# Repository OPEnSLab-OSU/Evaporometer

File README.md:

# OPEnS Lab Evaporometer

Here are documented all of the files and links regarding the evapor0meter. This includes all of code and CAD files to create and program the entire system. It also includes a link to the lastest data collected in the field. 

For an overview of the project view the [Evaporometer Wiki](https://github.com/OPEnSLab-OSU/OPEnS-Lab-Home/wiki/Evaporometer)

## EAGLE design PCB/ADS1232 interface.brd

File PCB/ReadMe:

Place to store archived EagleCAD PCB projects. Files shoudl have last data modified and version number in the name.

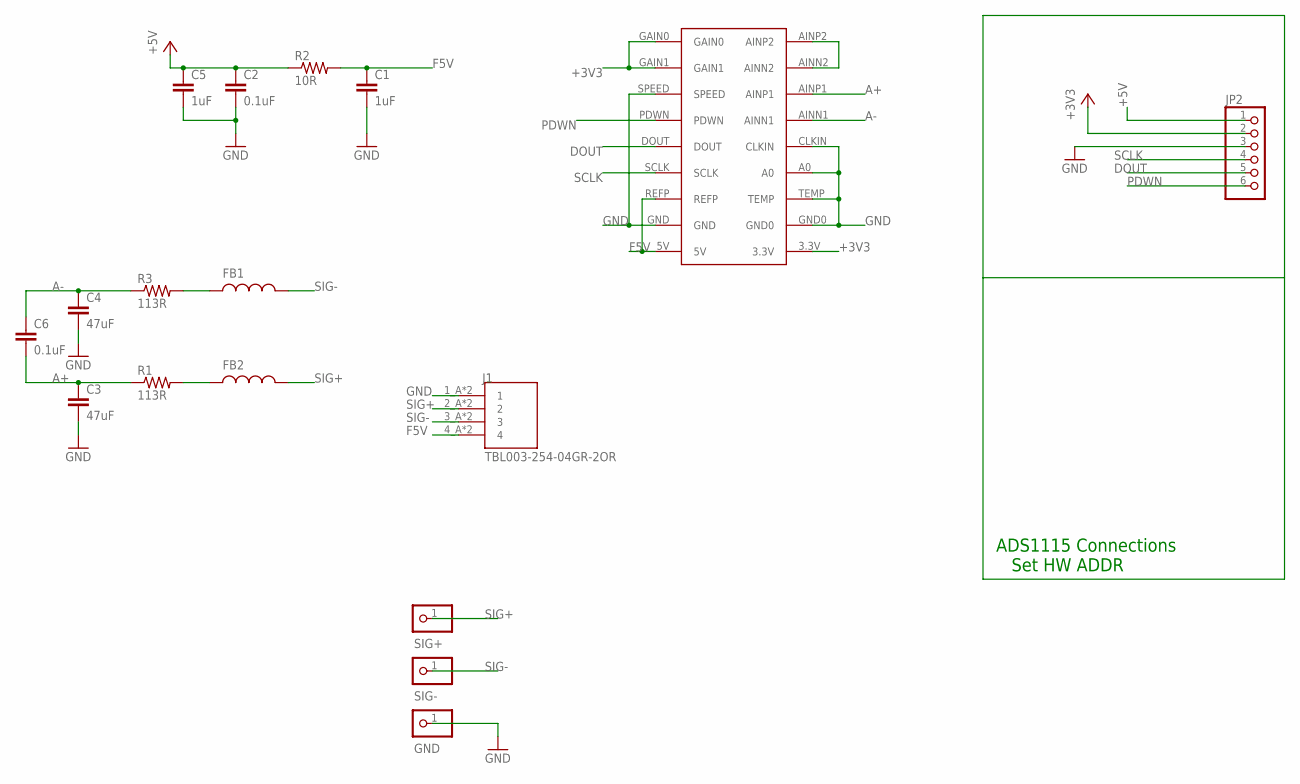
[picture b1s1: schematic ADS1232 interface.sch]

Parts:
ADS1232: ADS1232
C1, C5: 1uF; C0805
C2, C6: 0.1uF; C0805
C3, C4: 47uF; C0805
FB1, FB2: WE-RFI_0805A_744760282A; WE-RFI_0805A
GND: PINHD-1X1; 1X01
J1: TBL003-254-04GR-2OR; CUI_TBL003-254-04GR-2OR
JP2: PINHD-1X6; 1X06
R1, R3: 113R; R0805
R2: 10R; R0805
SIG+: PINHD-1X1; 1X01
SIG-: PINHD-1X1; 1X01

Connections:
+3V3: ADS1232.3.3V, ADS1232.GAIN0, ADS1232.GAIN1, JP2.2
+5V: C2.1, C5.1, JP2.1, R2.1
A+: ADS1232.AINP1, C3.1, C6.2, R1.1
A-: ADS1232.AINN1, C4.1, C6.1, R3.1
DOUT: ADS1232.DOUT, JP2.5
F5V: ADS1232.5V, ADS1232.REFP, C1.1, J1.4_A (4), J1.4_B (4), R2.2
GND: ADS1232.A0, ADS1232.AINN2, ADS1232.AINP2, ADS1232.CLKIN, ADS1232.GND, ADS1232.GND0, ADS1232.SPEED, ADS1232.TEMP, C1.2, C2.2, C3.2, C4.2, C5.2, GND.1, J1.1_A (1), J1.1_B (1), JP2.3
unnamed: FB1.1, R3.2
unnamed: FB2.1, R1.2
PDWN: ADS1232.PDWN, JP2.6
SCLK: ADS1232.SCLK, JP2.4
SIG+: FB2.2, J1.2_A (2), J1.2_B (2), SIG+.1
SIG-: FB1.2, J1.3_A (3), J1.3_B (3), SIG-.1

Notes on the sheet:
ADS1115 Connections Set HW ADDR

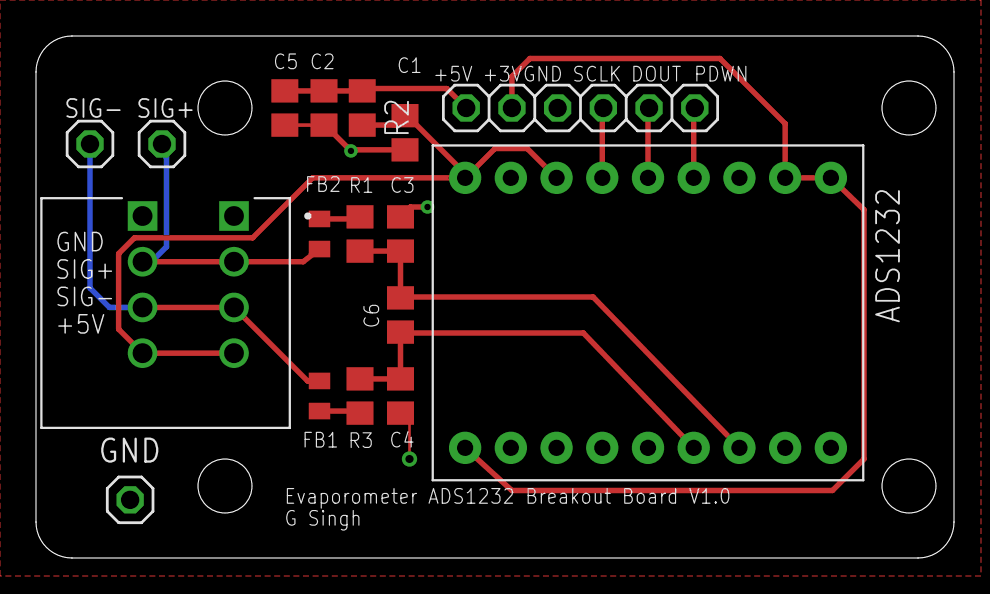
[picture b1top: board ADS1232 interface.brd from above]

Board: 2 copper layers, 51.0 x 29.0 mm, 17 parts (0 on the bottom side), 13 nets.

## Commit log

2017-03-24 Create SuperValidatorCalibration
    This example is from sparkfun and we only changed the output for the units and the calibration factor that it initially had to the one that works with our 2kg strain gauge.
2017-03-24 Create SuperValidatorDisplayMass
    This example uses that code from sparkfun and the only change was the calibration factor obtained from running the calibration code for this same project
2017-03-24 Create LinkToSTL
    Link to fusion360 download page
2017-03-24 Update LinkToSTL
2017-06-30 Rename LinkToSTL to LinkToSTL.md
2017-08-01 Add files via upload
    Receiver Assembly
2017-08-01 Rename ArduinoCode/SuperValidatorCalibration to ArduinoCode/Calibration/SuperValidatorCalibration
2017-08-01 Rename ArduinoCode/SuperValidatorDisplayMass to ArduinoCode/Calibration/SuperValidatorDisplayMass
2017-08-01 Add files via upload
    TransmitterModel
2017-08-01 Add files via upload
    These are the two current scripts for the Transmitter (tx) and Receiver (TestRec)
2017-08-01 Rename LoRa_tx_3x_transmit_mem_7.26.17.ino to Transmitter_Code/LoRa_tx_3x_transmit_mem_7.26.17.ino
2017-08-01 Create Receiver Code
2017-08-24 A useful diagram of Evaporometer connections
2018-01-16 Add files via upload
    Replacing old transmitter files
2018-01-16 Add files via upload
    Replacing old receiver code
2018-02-24 Uploaded V1 of EvapShark combo PCB
2018-03-06 Update evap_ethernet.ino
    Updates to existing code. Currently working test code.
2018-03-07 Transmitter update supports TSL2561 not TSL2591
    transitioning to light sensor version with re-addressable pins to support multiple sensors
2018-03-07 Transmitter with SD card storage (NO HUB needed)
    For data collection with just a transmitter and a SD card writer; no LoRa HUB/lora transmission required :)
2018-03-07 Rename Nelson_SDCard_2.27.18.ino to Transmitter_SDCard_2.27.18.ino
2018-03-07 Rename Transmitter_SDCard_2.27.18.ino to Data_collection_SDCard_2.27.18.ino
2018-03-07 Evaporometer PCB V1
2018-03-12 Evaporometer with SD card logging documentation
2018-03-22 Rename Description.md to README.md
2018-04-02 Add files via upload
    Updated Diagram for Evaporometer PCB
2018-04-02 Added Transmit code w/RF95 Manager. Added Decagon/Evap Hub code.
2018-04-04 Create test
2022-05-10 Add ADS1232 integration with Loom V3
2022-06-09 Add firmware w/ Loom-integrated ADS1232
2022-06-20 Removed out of date files. Added links and files for current version.
2022-06-30 Calibration and Field code versions, no battery or SHT30
2022-07-01 Evap code June 1, 2022: Load cell, SHT30, BatteryV
    Integrated Loom3 code for logging LoadCell ADS1232, Battery voltage, SHT30 temp humid
2023-04-17 Create OnePiece board
2025-03-14 Evaporometer Code Changes
2025-04-05 Created dupe branch
2025-04-14 Finished
2025-05-05 Add files via upload
    Current 2024 printed models
2025-05-05 moved old files into legacy
2026-04-27 Fix typo in README.md
2026-06-09 Add Evaporometer Rev 02 firmware

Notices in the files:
parts and their libraries:
Wurth_Elektronik_Passive_rev19e: Copyright: Würth Elektronik
